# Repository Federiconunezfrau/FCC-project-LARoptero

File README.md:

# FCC-project-LARoptero
This repository contains the hardware for the Flight Control Computer of the LARoptero project

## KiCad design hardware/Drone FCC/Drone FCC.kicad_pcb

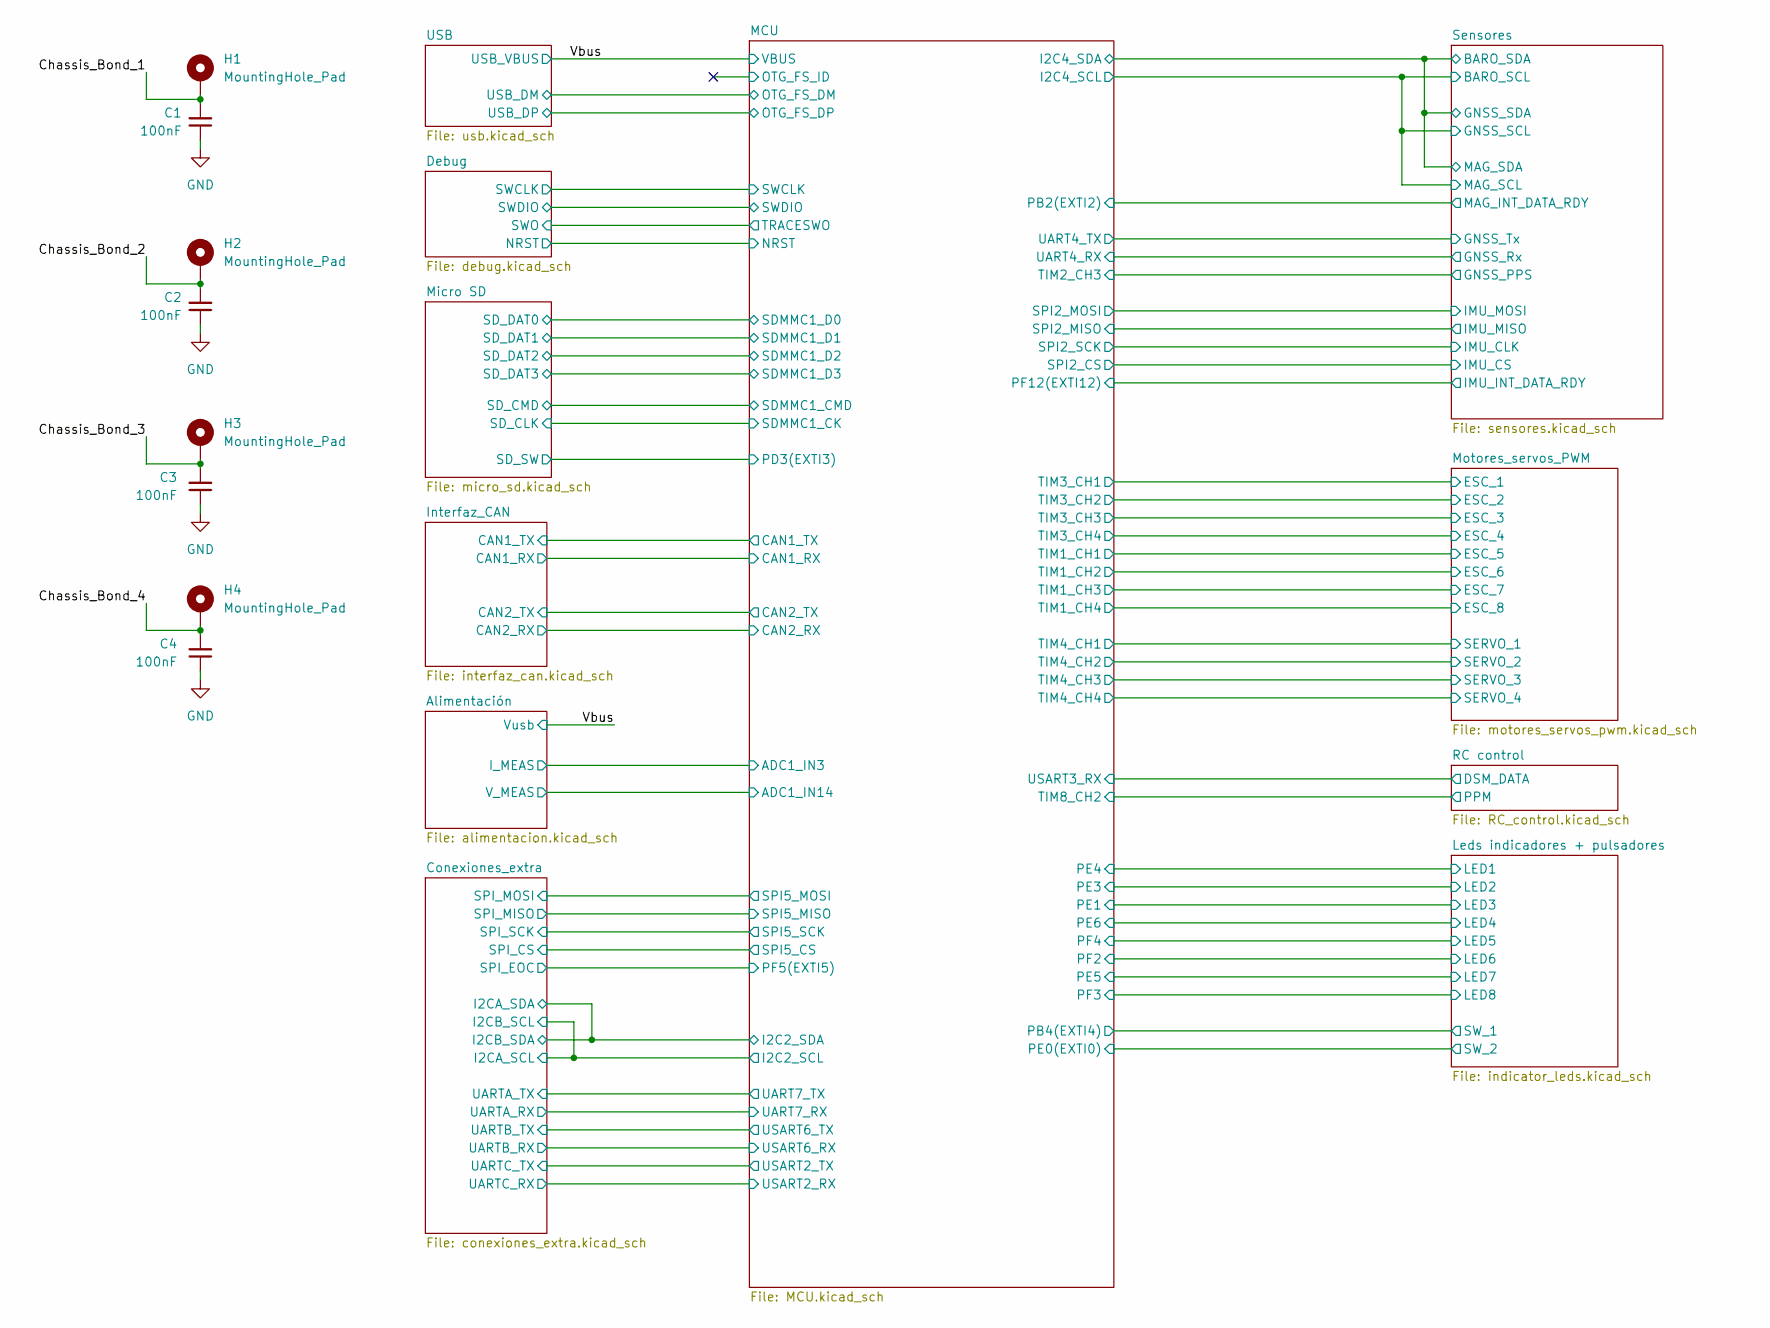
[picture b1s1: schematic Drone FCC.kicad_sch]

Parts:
C1, C2, C3, C4: 100nF; C_0402_1005Metric_Pad0.74x0.62mm_HandSolder
H1, H2, H3, H4: MountingHole_Pad; MountingHole_3.2mm_M3_Pad_TopBottom

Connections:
/Chassis_Bond_1: C1.2, H1.1
/Chassis_Bond_2: C2.2, H2.1
/Chassis_Bond_3: C3.2, H3.1
/Chassis_Bond_4: C4.2, H4.1
GND: C1.1, C2.1, C3.1, C4.1; also elsewhere on the board

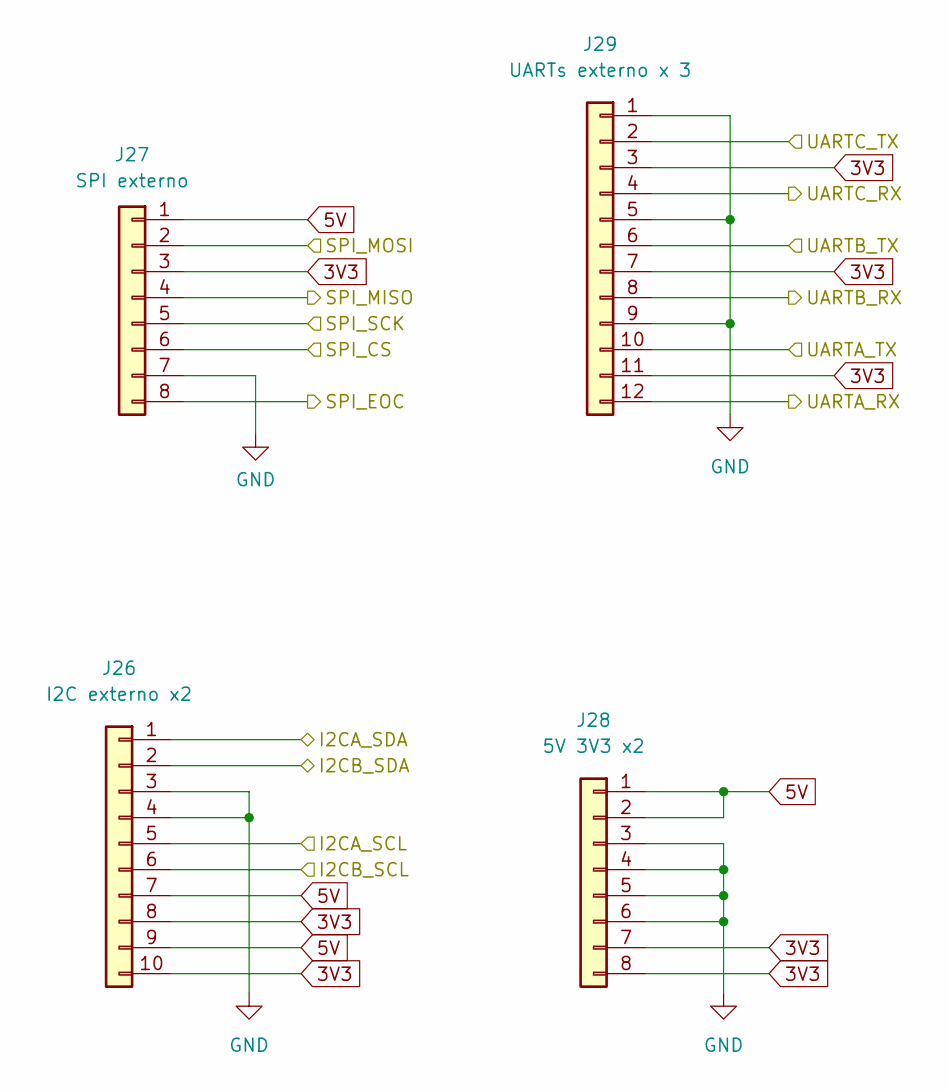
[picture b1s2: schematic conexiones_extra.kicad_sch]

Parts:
J26: I2C externo x2; PinHeader_2x05_P2.54mm_Horizontal
J27: SPI externo; PinHeader_2x04_P2.54mm_Horizontal
J28: 5V 3V3 x2; PinHeader_2x04_P2.54mm_Horizontal
J29: UARTs externo x 3; PinHeader_2x06_P2.54mm_Horizontal

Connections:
3V3: J26.8, J26.10, J27.3, J28.7, J28.8, J29.3, J29.7, J29.11; also elsewhere on the board
5V: J26.7, J26.9, J27.1, J28.1, J28.2; also elsewhere on the board
/Conexiones_extra/I2CA_SCL: J26.5, J26.6; also elsewhere on the board
/Conexiones_extra/I2CA_SDA: J26.1, J26.2; also elsewhere on the board
/Conexiones_extra/SPI_CS: J27.6; also elsewhere on the board
/Conexiones_extra/SPI_EOC: J27.8; also elsewhere on the board
/Conexiones_extra/SPI_MISO: J27.4; also elsewhere on the board
/Conexiones_extra/SPI_MOSI: J27.2; also elsewhere on the board
/Conexiones_extra/SPI_SCK: J27.5; also elsewhere on the board
/Conexiones_extra/UARTA_RX: J29.12; also elsewhere on the board
/Conexiones_extra/UARTA_TX: J29.10; also elsewhere on the board
/Conexiones_extra/UARTB_RX: J29.8; also elsewhere on the board
/Conexiones_extra/UARTB_TX: J29.6; also elsewhere on the board
/Conexiones_extra/UARTC_RX: J29.4; also elsewhere on the board
/Conexiones_extra/UARTC_TX: J29.2; also elsewhere on the board
GND: J26.3, J26.4, J27.7, J28.3, J28.4, J28.5, J28.6, J29.1, J29.5, J29.9; also elsewhere on the board

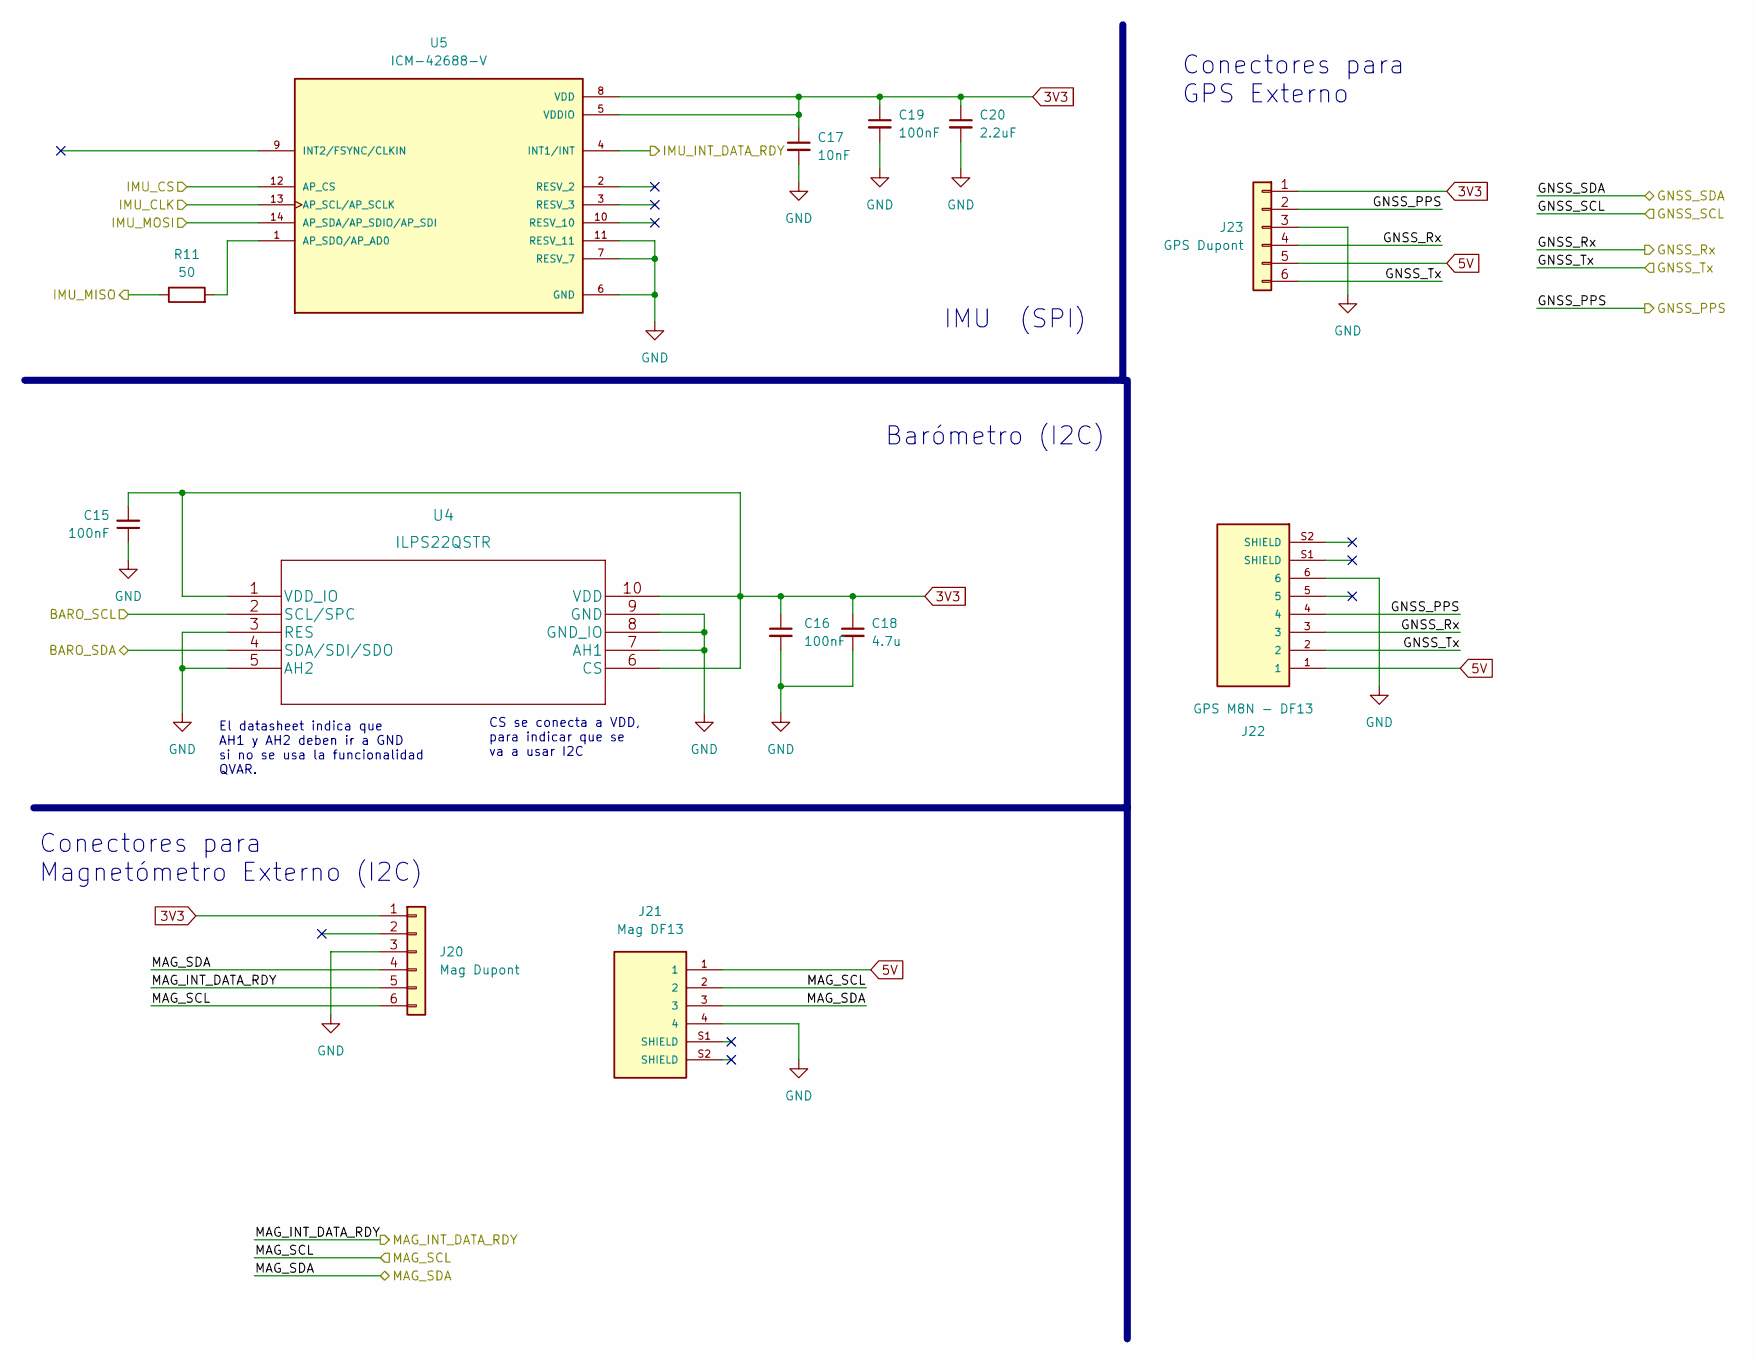
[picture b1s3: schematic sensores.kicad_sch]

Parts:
C15, C16, C19: 100nF; C_0402_1005Metric_Pad0.74x0.62mm_HandSolder
C17: 10nF; C_0402_1005Metric_Pad0.74x0.62mm_HandSolder
C18: 4.7u; C_0805_2012Metric_Pad1.18x1.45mm_HandSolder
C20: 2.2uF; C_0603_1608Metric_Pad1.08x0.95mm_HandSolder
J20: Mag Dupont; PinHeader_2x03_P2.54mm_Horizontal
J21: Mag DF13; Hirose_DF13C_CL535-0404-8-51_1x04-1MP_P1.25mm_Vertical; PARTREV N/A
J22: GPS M8N - DF13; HIROSE_DF13C-6P-1.25V(51); PARTREV N/A
J23: GPS Dupont; PinHeader_2x03_P2.54mm_Horizontal
R11: 50; R_0402_1005Metric_Pad0.72x0.64mm_HandSolder
U4: ILPS22QSTR
U5: ICM-42688-V; PQFN50P300X250X97-14N

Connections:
3V3: C15.2, C16.1, C17.1, C18.1, C19.1, C20.1, J20.1, J23.1, U4.1 (VDD_IO), U4.6 (CS), U4.10 (VDD), U5.5 (VDDIO), U5.8 (VDD); also elsewhere on the board
5V: J21.1, J22.1, J23.5; also elsewhere on the board
/MCU/PF12(EXTI12): U5.4 (INT1/INT); also elsewhere on the board
/MCU/SPI2_CS: U5.12 (AP_CS); also elsewhere on the board
/MCU/SPI2_MISO: R11.1; also elsewhere on the board
/MCU/SPI2_MOSI: U5.14 (AP_SDA/AP_SDIO/AP_SDI); also elsewhere on the board
/MCU/SPI2_SCK: U5.13 (AP_SCL/AP_SCLK); also elsewhere on the board
/Sensores/GNSS_PPS: J22.4, J23.2; also elsewhere on the board
/Sensores/GNSS_Rx: J22.3, J23.4; also elsewhere on the board
/Sensores/GNSS_SCL: J20.6, J21.2, U4.2 (SCL/SPC); also elsewhere on the board
/Sensores/GNSS_SDA: J20.4, J21.3, U4.4 (SDA/SDI/SDO); also elsewhere on the board
/Sensores/GNSS_Tx: J22.2, J23.6; also elsewhere on the board
/Sensores/MAG_INT_DATA_RDY: J20.5; also elsewhere on the board
GND: C15.1, C16.2, C17.2, C18.2, C19.2, C20.2, J20.3, J21.4, J22.6, J23.3, U4.3 (RES), U4.5 (AH2), U4.7 (AH1), U4.8 (GND_IO), U4.9 (GND), U5.6 (GND), U5.7 (RESV_7), U5.11 (RESV_11); also elsewhere on the board
unnamed: R11.2, U5.1 (AP_SDO/AP_AD0)

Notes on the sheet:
IMU (SPI)
Conectores para GPS Externo
El datasheet indica que AH1 y AH2 deben ir a GND si no se usa la funcionalidad QVAR.
CS se conecta a VDD, para indicar que se va a usar I2C
Conectores para Magnetómetro Externo (I2C)
Barómetro (I2C)

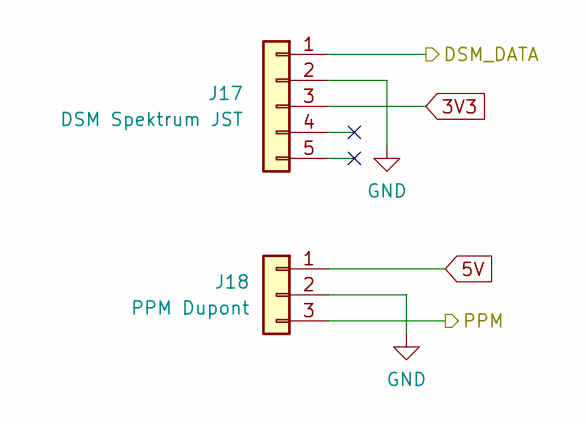
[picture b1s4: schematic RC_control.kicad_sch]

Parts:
J17: DSM Spektrum JST; JST-B3B-ZR-SM4-TFLFSN-0-0-MFG
J18: PPM Dupont; PinHeader_1x03_P2.54mm_Horizontal

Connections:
3V3: J17.3; also elsewhere on the board
5V: J18.1; also elsewhere on the board
/MCU/TIM8_CH2: J18.3; also elsewhere on the board
/MCU/USART3_RX: J17.1; also elsewhere on the board
GND: J17.2, J18.2; also elsewhere on the board

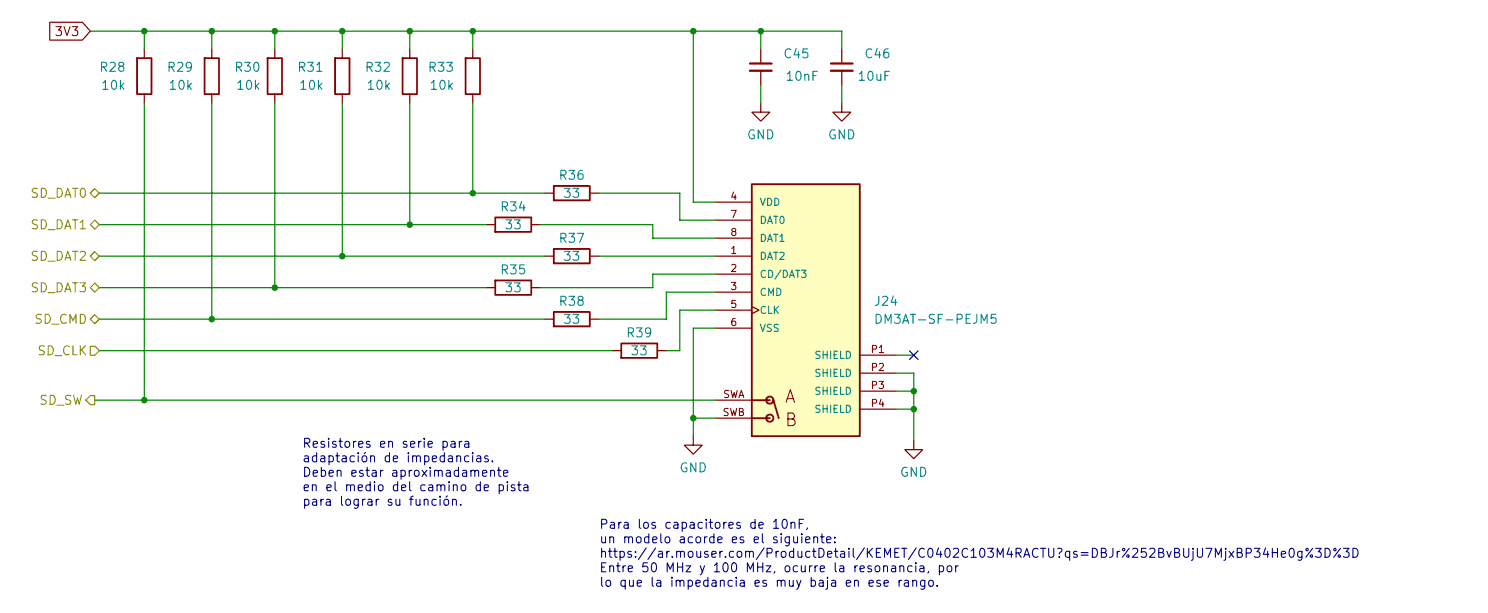
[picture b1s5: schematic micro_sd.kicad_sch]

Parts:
C45: 10nF; C_0402_1005Metric_Pad0.74x0.62mm_HandSolder
C46: 10uF; C_0603_1608Metric_Pad1.08x0.95mm_HandSolder
J24: DM3AT-SF-PEJM5; HRS_DM3AT-SF-PEJM5
R28, R29, R30, R31, R32, R33: 10k; R_0402_1005Metric_Pad0.72x0.64mm_HandSolder
R34, R35, R36, R37, R38, R39: 33; R_0402_1005Metric_Pad0.72x0.64mm_HandSolder

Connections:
3V3: C45.1, C46.1, J24.4 (VDD), R28.2, R29.2, R30.2, R31.2, R32.2, R33.2; also elsewhere on the board
/MCU/PD3(EXTI3): J24.SWA, R28.1; also elsewhere on the board
/MCU/SDMMC1_CK: R39.2; also elsewhere on the board
/MCU/SDMMC1_CMD: R29.1, R38.2; also elsewhere on the board
/MCU/SDMMC1_D0: R33.1, R36.2; also elsewhere on the board
/MCU/SDMMC1_D1: R32.1, R34.2; also elsewhere on the board
/MCU/SDMMC1_D2: R31.1, R37.2; also elsewhere on the board
/MCU/SDMMC1_D3: R30.1, R35.2; also elsewhere on the board
GND: C45.2, C46.2, J24.6 (VSS), J24.P2 (SHIELD), J24.P3 (SHIELD), J24.P4 (SHIELD), J24.SWB; also elsewhere on the board
unnamed: J24.1 (DAT2), R37.1
unnamed: J24.2 (CD/DAT3), R35.1
unnamed: J24.3 (CMD), R38.1
unnamed: J24.5 (CLK), R39.1
unnamed: J24.7 (DAT0), R36.1
unnamed: J24.8 (DAT1), R34.1

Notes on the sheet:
Para los capacitores de 10nF, un modelo acorde es el siguiente: https://ar.mouser.com/ProductDetail/KEMET/C0402C103M4RACTU?qs=DBJr%252BvBUjU7MjxBP34He0g%3D%3D Entre 50 MHz y 100 MHz, ocurre la resonancia, por lo que la impedancia es muy baja en ese rango.
Resistores en serie para adaptación de impedancias. Deben estar aproximadamente en el medio del camino de pista para lograr su función.

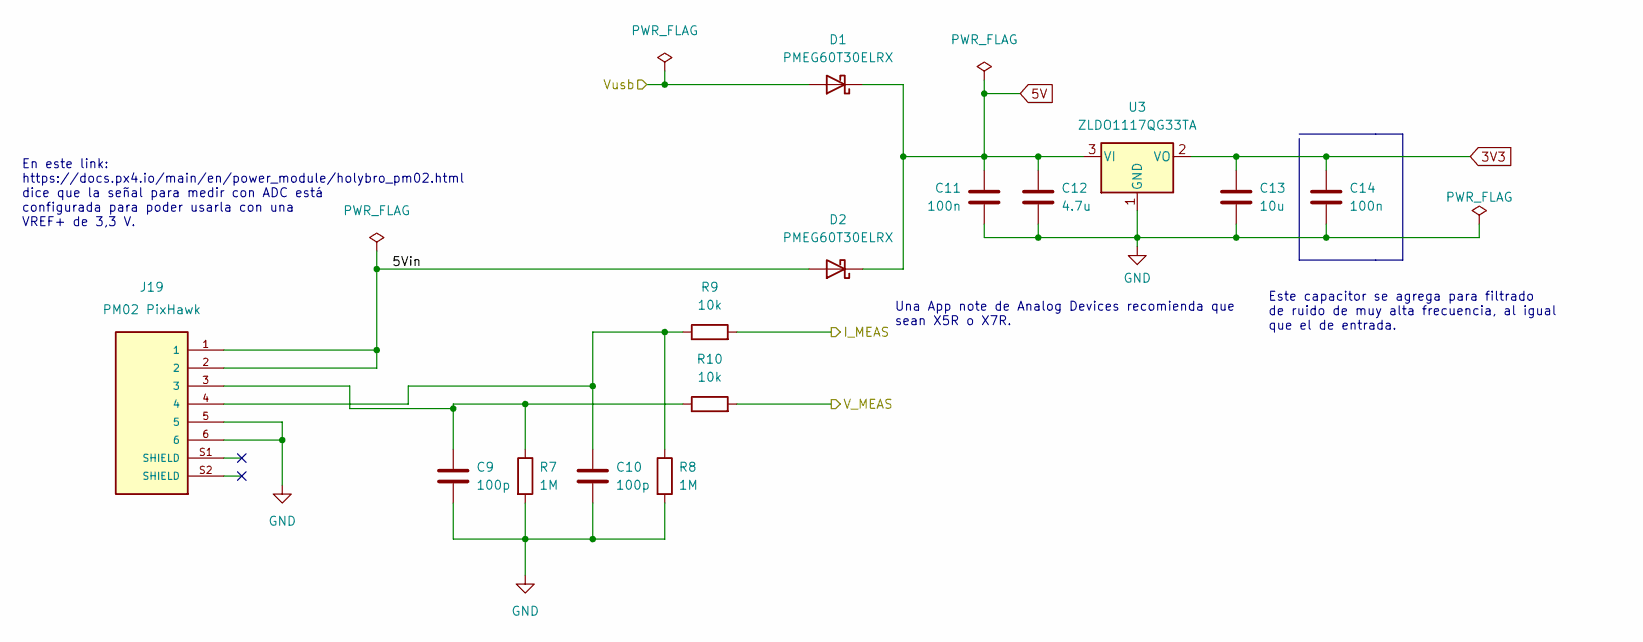
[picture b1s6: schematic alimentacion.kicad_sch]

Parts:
C9, C10: 100p; C_0402_1005Metric_Pad0.74x0.62mm_HandSolder
C11, C14: 100n; C_0603_1608Metric_Pad1.08x0.95mm_HandSolder
C12: 4.7u; C_1206_3216Metric_Pad1.33x1.80mm_HandSolder
C13: 10u; CAPC3216X110N
D1, D2: PMEG60T30ELRX; SODFL3517X110N
J19: PM02 PixHawk; HIROSE_DF13C-6P-1.25V(51); PARTREV N/A
R7, R8: 1M; R_0402_1005Metric_Pad0.72x0.64mm_HandSolder
R9, R10: 10k; R_0402_1005Metric_Pad0.72x0.64mm_HandSolder
U3: ZLDO1117QG33TA; SOT-223-3_TabPin2

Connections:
3V3: C13.1, C14.1, U3.2 (VO); also elsewhere on the board
5V: C11.2, C12.1, D1.1 (K), D2.1 (K), U3.3 (VI); also elsewhere on the board
/Alimentación/5Vin: D2.2 (A), J19.1, J19.2
/Alimentación/I_MEAS: R9.2; also elsewhere on the board
/Alimentación/V_MEAS: R10.2; also elsewhere on the board
/Vbus: D1.2 (A); also elsewhere on the board
GND: C9.2, C10.2, C11.1, C12.2, C13.2, C14.2, J19.5, J19.6, R7.2, R8.2, U3.1 (GND); also elsewhere on the board
unnamed: C9.1, J19.3, R7.1, R10.1
unnamed: C10.1, J19.4, R8.1, R9.1

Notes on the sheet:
Este capacitor se agrega para filtrado de ruido de muy alta frecuencia, al igual que el de entrada.
En este link: https://docs.px4.io/main/en/power_module/holybro_pm02.html dice que la señal para medir con ADC está configurada para poder usarla con una VREF+ de 3,3 V.
Una App note de Analog Devices recomienda que sean X5R o X7R.

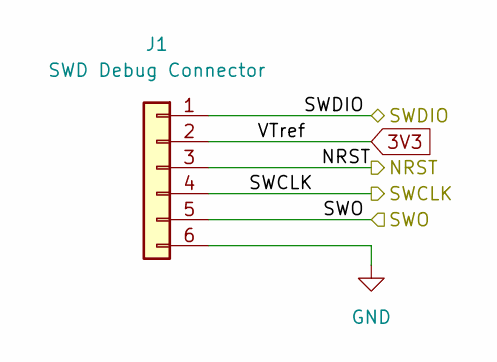
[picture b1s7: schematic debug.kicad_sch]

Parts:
J1: SWD Debug Connector; PinHeader_2x03_P2.54mm_Vertical

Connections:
3V3: J1.2; also elsewhere on the board
/Debug/NRST: J1.3; also elsewhere on the board
/Debug/SWCLK: J1.4; also elsewhere on the board
/Debug/SWDIO: J1.1; also elsewhere on the board
/Debug/SWO: J1.5; also elsewhere on the board
GND: J1.6; also elsewhere on the board

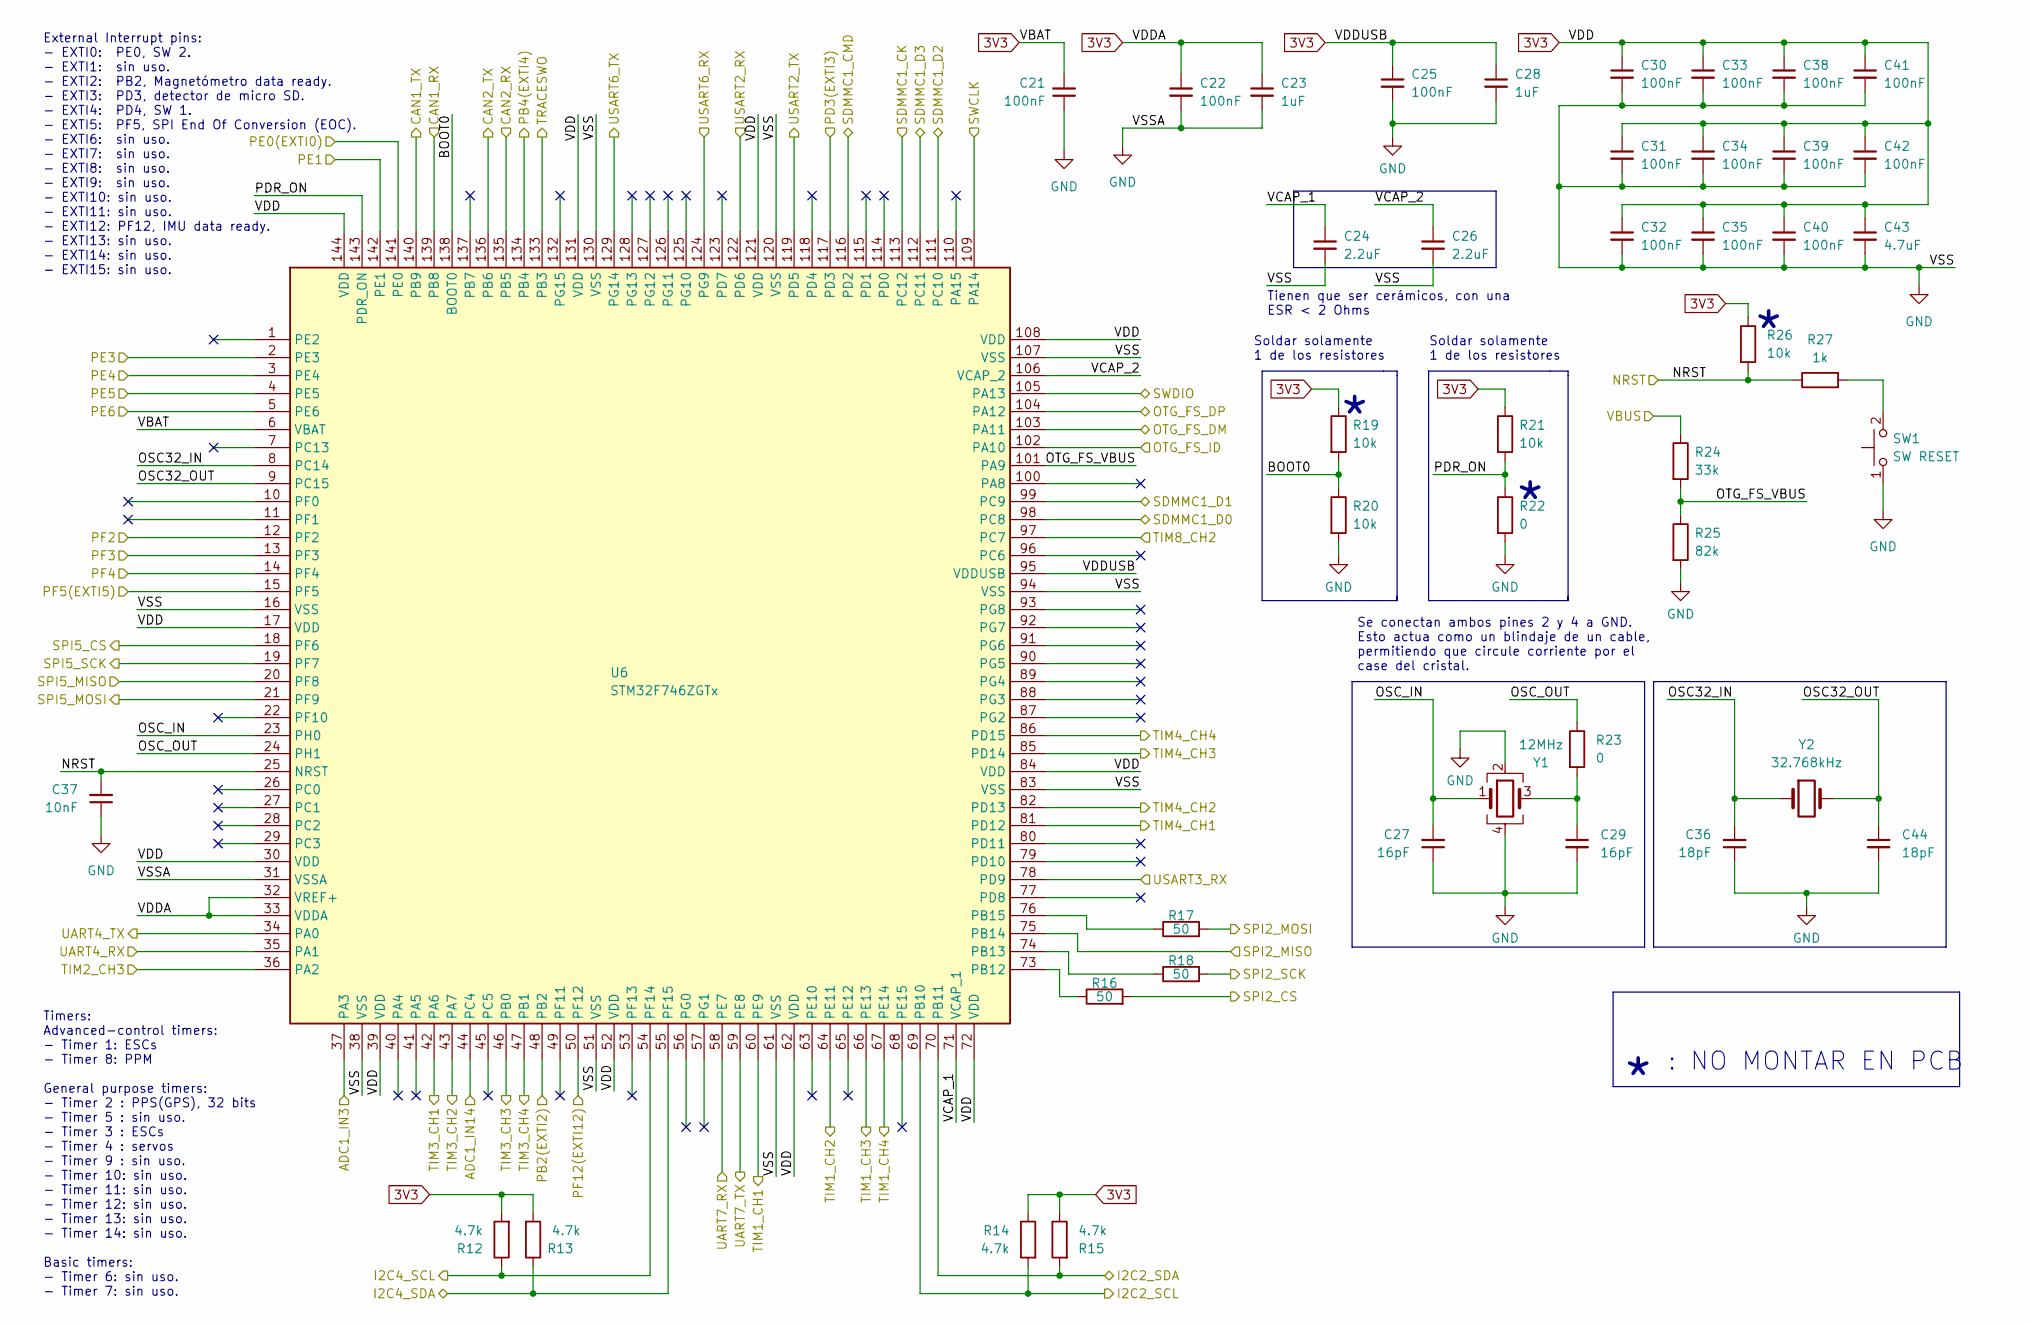
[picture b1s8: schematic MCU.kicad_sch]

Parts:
C21, C22, C25, C30, C31, C32, C33, C34, C35, C38, C39, C40, C41, C42: 100nF; C_0402_1005Metric_Pad0.74x0.62mm_HandSolder
C23, C28: 1uF; C_0805_2012Metric_Pad1.18x1.45mm_HandSolder
C24, C26: 2.2uF; C_0402_1005Metric_Pad0.74x0.62mm_HandSolder
C27, C29: 16pF; C_0402_1005Metric_Pad0.74x0.62mm_HandSolder
C36, C44: 18pF; C_0402_1005Metric_Pad0.74x0.62mm_HandSolder
C37: 10nF; C_0402_1005Metric_Pad0.74x0.62mm_HandSolder
C43: 4.7uF; C_0603_1608Metric_Pad1.08x0.95mm_HandSolder
R12, R13, R14, R15: 4.7k; R_0402_1005Metric_Pad0.72x0.64mm_HandSolder
R16, R17, R18: 50; R_0402_1005Metric_Pad0.72x0.64mm_HandSolder
R19, R20, R21, R26: 10k; R_0402_1005Metric_Pad0.72x0.64mm_HandSolder
R22, R23: 0; R_0402_1005Metric_Pad0.72x0.64mm_HandSolder
R24: 33k; R_0402_1005Metric_Pad0.72x0.64mm_HandSolder
R25: 82k; R_0402_1005Metric_Pad0.72x0.64mm_HandSolder
R27: 1k; R_0402_1005Metric_Pad0.72x0.64mm_HandSolder
SW1: SW RESET; 434121043816
U6: STM32F746ZGTx; LQFP-144_20x20mm_P0.5mm
Y1: 12MHz; XTAL_ECS-120-8-33Q-RES-TR
Y2: 32.768kHz; ECS-.327-9-34QN-TR

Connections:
3V3: C21.2, C22.1, C23.1, C25.1, C28.1, C30.1, C31.1, C32.1, C33.1, C34.1, C35.1, C38.1, C39.1, C40.1, C41.1, C42.1, C43.1, R12.2, R13.2, R14.1, R15.1, R19.1, R21.1, R26.1, U6.6 (VBAT), U6.17 (VDD), U6.30 (VDD), U6.32 (VREF+), U6.33 (VDDA), U6.39 (VDD), U6.52 (VDD), U6.62 (VDD), U6.72 (VDD), U6.84 (VDD), U6.95 (VDDUSB), U6.108 (VDD), U6.121 (VDD), U6.131 (VDD), U6.144 (VDD); also elsewhere on the board
/Alimentación/I_MEAS: U6.37 (PA3); also elsewhere on the board
/Alimentación/V_MEAS: U6.44 (PC4); also elsewhere on the board
/Conexiones_extra/I2CA_SCL: R14.2, U6.69 (PB10); also elsewhere on the board
/Conexiones_extra/I2CA_SDA: R15.2, U6.70 (PB11); also elsewhere on the board
/Conexiones_extra/SPI_CS: U6.18 (PF6); also elsewhere on the board
/Conexiones_extra/SPI_EOC: U6.15 (PF5); also elsewhere on the board
/Conexiones_extra/SPI_MISO: U6.20 (PF8); also elsewhere on the board
/Conexiones_extra/SPI_MOSI: U6.21 (PF9); also elsewhere on the board
/Conexiones_extra/SPI_SCK: U6.19 (PF7); also elsewhere on the board
/Conexiones_extra/UARTA_RX: U6.58 (PE7); also elsewhere on the board
/Conexiones_extra/UARTA_TX: U6.59 (PE8); also elsewhere on the board
/Conexiones_extra/UARTB_RX: U6.124 (PG9); also elsewhere on the board
/Conexiones_extra/UARTB_TX: U6.129 (PG14); also elsewhere on the board
/Conexiones_extra/UARTC_RX: U6.122 (PD6); also elsewhere on the board
/Conexiones_extra/UARTC_TX: U6.119 (PD5); also elsewhere on the board
/Debug/NRST: C37.2, R26.2, R27.1, U6.25 (NRST); also elsewhere on the board
/Debug/SWCLK: U6.109 (PA14); also elsewhere on the board
/Debug/SWDIO: U6.105 (PA13); also elsewhere on the board
/Debug/SWO: U6.133 (PB3); also elsewhere on the board
/Interfaz_CAN/CAN1_RX: U6.139 (PB8); also elsewhere on the board
/Interfaz_CAN/CAN1_TX: U6.140 (PB9); also elsewhere on the board
/Interfaz_CAN/CAN2_RX: U6.135 (PB5); also elsewhere on the board
/Interfaz_CAN/CAN2_TX: U6.136 (PB6); also elsewhere on the board
/Leds indicadores + pulsadores/LED1: U6.3 (PE4); also elsewhere on the board
/Leds indicadores + pulsadores/LED2: U6.2 (PE3); also elsewhere on the board
/Leds indicadores + pulsadores/LED3: U6.142 (PE1); also elsewhere on the board
/Leds indicadores + pulsadores/LED4: U6.5 (PE6); also elsewhere on the board
/Leds indicadores + pulsadores/LED5: U6.14 (PF4); also elsewhere on the board
/Leds indicadores + pulsadores/LED6: U6.12 (PF2); also elsewhere on the board
/Leds indicadores + pulsadores/LED7: U6.4 (PE5); also elsewhere on the board
/Leds indicadores + pulsadores/LED8: U6.13 (PF3); also elsewhere on the board
/Leds indicadores + pulsadores/SW_1: U6.134 (PB4); also elsewhere on the board
/Leds indicadores + pulsadores/SW_2: U6.141 (PE0); also elsewhere on the board
/MCU/BOOT0: R19.2, R20.1, U6.138 (BOOT0)
/MCU/OSC32_IN: C36.2, U6.8 (PC14), Y2.1
/MCU/OSC32_OUT: C44.1, U6.9 (PC15), Y2.2
/MCU/OSC_IN: C27.2, U6.23 (PH0), Y1.1
/MCU/OSC_OUT: R23.1, U6.24 (PH1)
/MCU/OTG_FS_ID: U6.102 (PA10)
/MCU/OTG_FS_VBUS: R24.2, R25.1, U6.101 (PA9)
/MCU/PD3(EXTI3): U6.117 (PD3); also elsewhere on the board
/MCU/PDR_ON: R21.2, R22.1, U6.143 (PDR_ON)
/MCU/PF12(EXTI12): U6.50 (PF12); also elsewhere on the board
/MCU/SDMMC1_CK: U6.113 (PC12); also elsewhere on the board
/MCU/SDMMC1_CMD: U6.116 (PD2); also elsewhere on the board
/MCU/SDMMC1_D0: U6.98 (PC8); also elsewhere on the board
/MCU/SDMMC1_D1: U6.99 (PC9); also elsewhere on the board
/MCU/SDMMC1_D2: U6.111 (PC10); also elsewhere on the board
/MCU/SDMMC1_D3: U6.112 (PC11); also elsewhere on the board
/MCU/SPI2_CS: R16.2; also elsewhere on the board
/MCU/SPI2_MISO: U6.75 (PB14); also elsewhere on the board
/MCU/SPI2_MOSI: R17.2; also elsewhere on the board
/MCU/SPI2_SCK: R18.2; also elsewhere on the board
/MCU/TIM1_CH1: U6.60 (PE9); also elsewhere on the board
/MCU/TIM1_CH2: U6.64 (PE11); also elsewhere on the board
/MCU/TIM1_CH3: U6.66 (PE13); also elsewhere on the board
/MCU/TIM1_CH4: U6.67 (PE14); also elsewhere on the board
/MCU/TIM3_CH1: U6.42 (PA6); also elsewhere on the board
/MCU/TIM3_CH2: U6.43 (PA7); also elsewhere on the board
/MCU/TIM3_CH3: U6.46 (PB0); also elsewhere on the board
/MCU/TIM3_CH4: U6.47 (PB1); also elsewhere on the board
/MCU/TIM4_CH1: U6.81 (PD12); also elsewhere on the board
/MCU/TIM4_CH2: U6.82 (PD13); also elsewhere on the board
/MCU/TIM4_CH3: U6.85 (PD14); also elsewhere on the board
/MCU/TIM4_CH4: U6.86 (PD15); also elsewhere on the board
/MCU/TIM8_CH2: U6.97 (PC7); also elsewhere on the board
/MCU/USART3_RX: U6.78 (PD9); also elsewhere on the board
/MCU/VCAP_1: C24.1, U6.71 (VCAP_1)
/MCU/VCAP_2: C26.1, U6.106 (VCAP_2)
/Sensores/GNSS_PPS: U6.36 (PA2); also elsewhere on the board
/Sensores/GNSS_Rx: U6.35 (PA1); also elsewhere on the board
/Sensores/GNSS_SCL: R12.1, U6.54 (PF14); also elsewhere on the board
/Sensores/GNSS_SDA: R13.1, U6.55 (PF15); also elsewhere on the board
/Sensores/GNSS_Tx: U6.34 (PA0); also elsewhere on the board
/Sensores/MAG_INT_DATA_RDY: U6.48 (PB2); also elsewhere on the board
/USB/D+: U6.104 (PA12); also elsewhere on the board
/USB/D-: U6.103 (PA11); also elsewhere on the board
/Vbus: R24.1; also elsewhere on the board
GND: C21.1, C22.2, C23.2, C24.2, C25.2, C26.2, C27.1, C28.2, C29.2, C30.2, C31.2, C32.2, C33.2, C34.2, C35.2, C36.1, C37.1, C38.2, C39.2, C40.2, C41.2, C42.2, C43.2, C44.2, R20.2, R22.2, R25.2, SW1.1 (A), U6.16 (VSS), U6.31 (VSSA), U6.38 (VSS), U6.51 (VSS), U6.61 (VSS), U6.83 (VSS), U6.94 (VSS), U6.107 (VSS), U6.120 (VSS), U6.130 (VSS), Y1.2, Y1.4; also elsewhere on the board
unnamed: C29.1, R23.2, Y1.3
unnamed: R16.1, U6.73 (PB12)
unnamed: R17.1, U6.76 (PB15)
unnamed: R18.1, U6.74 (PB13)
unnamed: R27.2, SW1.2 (B)

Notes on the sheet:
Soldar solamente 1 de los resistores
: NO MONTAR EN PCB
Se conectan ambos pines 2 y 4 a GND. Esto actua como un blindaje de un cable, permitiendo que circule corriente por el case del cristal.
External Interrupt pins: - EXTI0: PE0, SW 2. - EXTI1: sin uso. - EXTI2: PB2, Magnetómetro data ready. - EXTI3: PD3, detector de micro SD. - EXTI4: PD4, SW 1. - EXTI5: PF5, SPI End Of Conversion (EOC). - EXTI6: sin uso. - EXTI7: sin uso. - EXTI8: sin uso. - EXTI9: sin uso. - EXTI10: sin uso. - EXTI1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
Tienen que ser cerámicos, con una ESR < 2 Ohms
Timers: Advanced-control timers: - Timer 1: ESCs - Timer 8: PPM General purpose timers: - Timer 2 : PPS(GPS), 32 bits - Timer 5 : sin uso. - Timer 3 : ESCs - Timer 4 : servos - Timer 9 : sin uso. - Timer 10: sin uso. - Timer 11: sin uso. - Timer 12: sin uso. - Timer 13: sin uso. - Timer 14: sin uso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

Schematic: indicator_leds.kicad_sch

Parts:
C47, C48: 10nF; C_0402_1005Metric_Pad0.74x0.62mm_HandSolder
D3, D5: LED_YELLOW; LED_0805_2012Metric_Pad1.15x1.40mm_HandSolder
D4, D6: LED_RED; LED_0805_2012Metric_Pad1.15x1.40mm_HandSolder
D7, D9: LED_GREEN; LED_0805_2012Metric_Pad1.15x1.40mm_HandSolder
D8, D10: LED_BLUE; LED_0805_2012Metric_Pad1.15x1.40mm_HandSolder
Q1, Q2, Q3, Q4, Q5, Q6, Q7, Q8: 2N7002; SOT-23
R40, R48: 10k; R_0402_1005Metric_Pad0.72x0.64mm_HandSolder
R41, R53: 1k; R_0402_1005Metric_Pad0.72x0.64mm_HandSolder
R42, R43, R49, R50, R56, R57, R62, R63: 100k; R_0402_1005Metric_Pad0.72x0.64mm_HandSolder
R44, R45, R51, R52, R58, R59, R64, R65: 33k; R_0402_1005Metric_Pad0.72x0.64mm_HandSolder
R46, R47, R54, R55, R60, R61, R66, R67: 220; R_0402_1005Metric_Pad0.72x0.64mm_HandSolder
SW2, SW3: SW Proposito General; 434121043816

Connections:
3V3: D3.2 (A), D4.2 (A), D5.2 (A), D6.2 (A), D7.2 (A), D8.2 (A), D9.2 (A), D10.2 (A), R40.1, R48.1; also elsewhere on the board
/Leds indicadores + pulsadores/LED1: R43.2, R45.1; also elsewhere on the board
/Leds indicadores + pulsadores/LED2: R56.2, R58.1; also elsewhere on the board
/Leds indicadores + pulsadores/LED3: R50.2, R52.1; also elsewhere on the board
/Leds indicadores + pulsadores/LED4: R62.2, R64.1; also elsewhere on the board
/Leds indicadores + pulsadores/LED5: R42.2, R44.1; also elsewhere on the board
/Leds indicadores + pulsadores/LED6: R49.2, R51.1; also elsewhere on the board
/Leds indicadores + pulsadores/LED7: R57.2, R59.1; also elsewhere on the board
/Leds indicadores + pulsadores/LED8: R63.2, R65.1; also elsewhere on the board
/Leds indicadores + pulsadores/SW_1: C47.2, R40.2, R41.1; also elsewhere on the board
/Leds indicadores + pulsadores/SW_2: C48.2, R48.2, R53.1; also elsewhere on the board
GND: C47.1, C48.1, Q1.2 (S), Q2.2 (S), Q3.2 (S), Q4.2 (S), Q5.2 (S), Q6.2 (S), Q7.2 (S), Q8.2 (S), R42.1, R43.1, R49.1, R50.1, R56.1, R57.1, R62.1, R63.1, SW2.1 (A), SW3.1 (A); also elsewhere on the board
unnamed: D3.1 (K), R46.2
unnamed: D4.1 (K), R47.2
unnamed: D5.1 (K), R54.2
unnamed: D6.1 (K), R55.2
unnamed: D7.1 (K), R60.2
unnamed: D8.1 (K), R61.2
unnamed: D9.1 (K), R66.2
unnamed: D10.1 (K), R67.2
unnamed: Q1.1 (G), R44.2
unnamed: Q2.1 (G), R45.2
unnamed: Q2.3 (D), R47.1
unnamed: Q3.1 (G), R51.2
unnamed: Q3.3 (D), R54.1
unnamed: Q4.1 (G), R52.2
unnamed: Q4.3 (D), R55.1
unnamed: Q5.1 (G), R58.2
unnamed: Q5.3 (D), R60.1
unnamed: Q6.1 (G), R59.2
unnamed: Q7.1 (G), R64.2
unnamed: Q7.3 (D), R66.1
unnamed: Q8.1 (G), R65.2
unnamed: R41.2, SW2.2 (B)
unnamed: R53.2, SW3.2 (B)

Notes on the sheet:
LEDs: 1) Board powered. 2) USB connected. 3) uSD present. 4) New GPS measurement received. 5) CAN 1 bus status. 6) CAN 2 bus status. 7) General purpose. 8) General purpose.

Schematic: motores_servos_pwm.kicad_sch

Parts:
J2: ESC 1; SAMTEC_TSW-101-08-G-T-RA
J3: ESC 2; SAMTEC_TSW-101-08-G-T-RA
J4: ESC 3; SAMTEC_TSW-101-08-G-T-RA
J5: ESC 4; SAMTEC_TSW-101-08-G-T-RA
J6: ESC 5; SAMTEC_TSW-101-08-G-T-RA
J7: ESC 6; SAMTEC_TSW-101-08-G-T-RA
J8: ESC 7; SAMTEC_TSW-101-08-G-T-RA
J9: ESC 8; SAMTEC_TSW-101-08-G-T-RA
J10: Power Servo; PHOENIX_1935161
J11: SERVO 1; SAMTEC_TSW-101-08-G-T-RA
J12: SERVO 2; SAMTEC_TSW-101-08-G-T-RA
J13: SERVO 3; SAMTEC_TSW-101-08-G-T-RA
J14: SERVO 4; SAMTEC_TSW-101-08-G-T-RA
JP1: SolderJumper_2_Open; SolderJumper-2_P1.3mm_Open_Pad1.0x1.5mm

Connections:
/MCU/TIM1_CH1: J6.1; also elsewhere on the board
/MCU/TIM1_CH2: J7.1; also elsewhere on the board
/MCU/TIM1_CH3: J8.1; also elsewhere on the board
/MCU/TIM1_CH4: J9.1; also elsewhere on the board
/MCU/TIM3_CH1: J2.1; also elsewhere on the board
/MCU/TIM3_CH2: J3.1; also elsewhere on the board
/MCU/TIM3_CH3: J4.1; also elsewhere on the board
/MCU/TIM3_CH4: J5.1; also elsewhere on the board
/MCU/TIM4_CH1: J11.1; also elsewhere on the board
/MCU/TIM4_CH2: J12.1; also elsewhere on the board
/MCU/TIM4_CH3: J13.1; also elsewhere on the board
/MCU/TIM4_CH4: J14.1; also elsewhere on the board
/Motores_servos_PWM/Vdd_ESC: J2.2, J3.2, J4.2, J5.2, J6.2, J7.2, J8.2, J9.2, JP1.1 (A)
/Motores_servos_PWM/Vdd_servos: J10.1, J11.2, J12.2, J13.2, J14.2, JP1.2 (B)
GND: J2.3, J3.3, J4.3, J5.3, J6.3, J7.3, J8.3, J9.3, J10.2, J11.3, J12.3, J13.3, J14.3; also elsewhere on the board

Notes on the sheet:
Headers Dupont Servos
Headers Dupont ESC

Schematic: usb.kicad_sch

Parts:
J25: Micro USB - B; MOLEX_105017-0001
R68: 0; R_0402_1005Metric_Pad0.72x0.64mm_HandSolder
U7: USBLC6-2SC6; SOT-23-6

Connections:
/USB/D+: U7.4 (I/O2); also elsewhere on the board
/USB/D-: U7.6 (I/O1); also elsewhere on the board
/USB/D_connector+: J25.3 (D+), U7.3 (I/O2)
/USB/D_connector-: J25.2 (D-), U7.1 (I/O1)
/USB/SHIELD_USB: J25.6 (SHIELD), J25.7 (MOUNT_1), R68.1
/Vbus: J25.1 (VDD), U7.5 (VBUS); also elsewhere on the board
GND: J25.5 (GND), R68.2, U7.2 (GND); also elsewhere on the board

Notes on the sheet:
El pin ID se deja abierto, ya que solo se utiliza el modo 'device'
: NO MONTAR EN PCB
